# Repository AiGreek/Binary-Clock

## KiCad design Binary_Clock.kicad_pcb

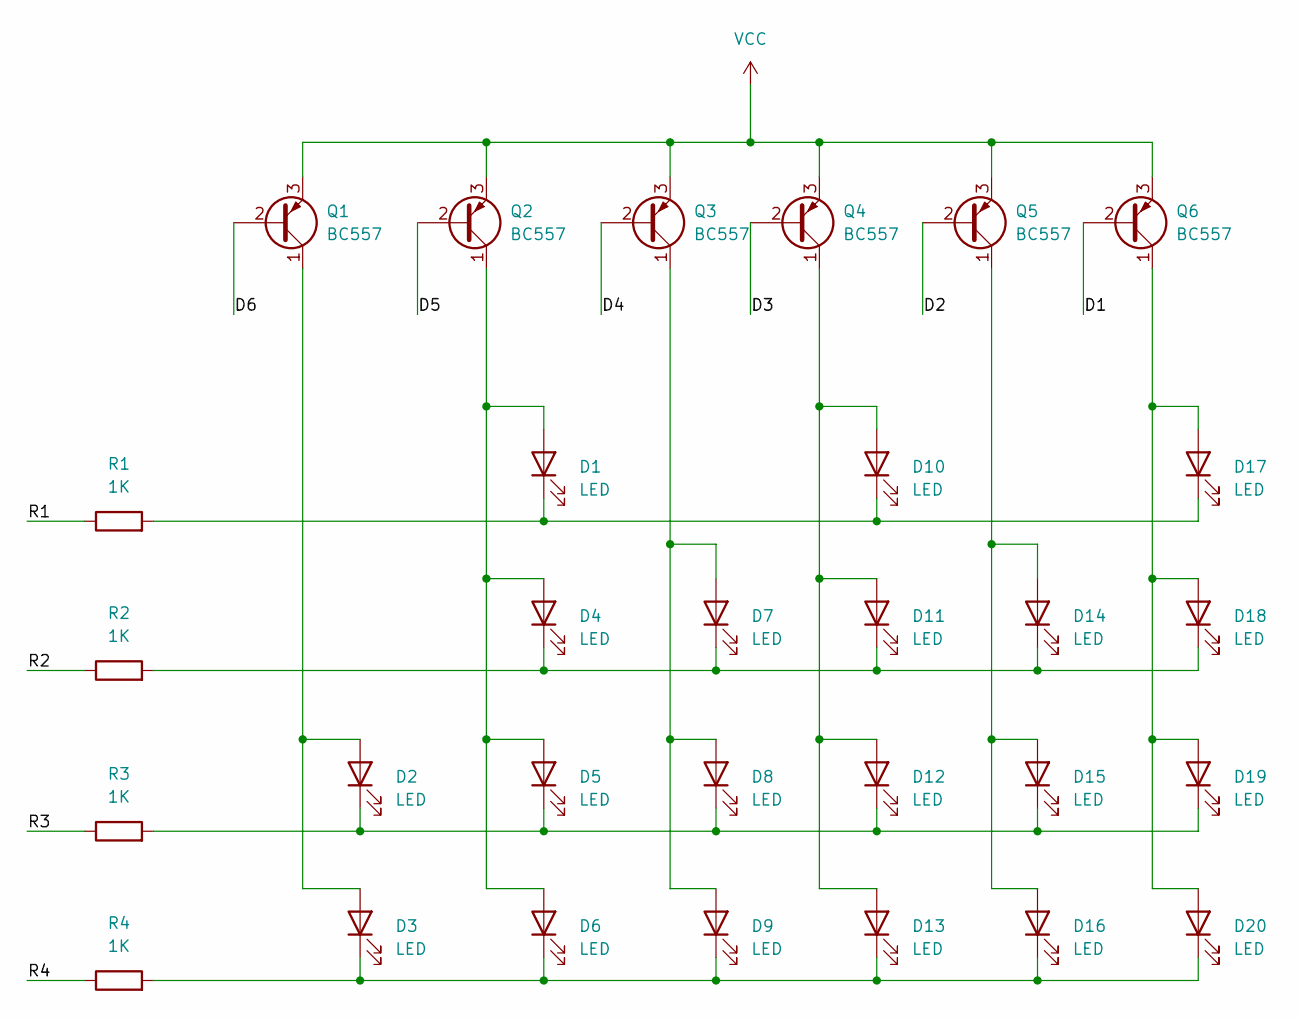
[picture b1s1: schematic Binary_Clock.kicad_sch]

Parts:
D1, D2, D3, D4, D5, D6, D7, D8, D9, D10, D11, D12, D13, D14, D15, D16, D17, D18, D19, D20: LED; LED_D5.0mm
Q1, Q2, Q3, Q4, Q5, Q6: BC557; TO-92_Inline
R1, R2, R3, R4: 1K; R_0805_2012Metric

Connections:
/D1: Q6.2 (B)
/D2: Q5.2 (B)
/D3: Q4.2 (B)
/D4: Q3.2 (B)
/D5: Q2.2 (B)
/D6: Q1.2 (B)
/R1: R1.1
/R2: R2.1
/R3: R3.1
/R4: R4.1
unnamed: D1.1 (K), D10.1 (K), D17.1 (K), R1.2
unnamed: D1.2 (A), D4.2 (A), D5.2 (A), D6.2 (A), Q2.1 (C)
unnamed: D2.2 (A), D3.2 (A), Q1.1 (C)
unnamed: D7.2 (A), D8.2 (A), D9.2 (A), Q3.1 (C)
unnamed: D10.2 (A), D11.2 (A), D12.2 (A), D13.2 (A), Q4.1 (C)
unnamed: D4.1 (K), D7.1 (K), D11.1 (K), D14.1 (K), D18.1 (K), R2.2
unnamed: D2.1 (K), D5.1 (K), D8.1 (K), D12.1 (K), D15.1 (K), D19.1 (K), R3.2
unnamed: D3.1 (K), D6.1 (K), D9.1 (K), D13.1 (K), D16.1 (K), D20.1 (K), R4.2
unnamed: D14.2 (A), D15.2 (A), D16.2 (A), Q5.1 (C)
unnamed: D17.2 (A), D18.2 (A), D19.2 (A), D20.2 (A), Q6.1 (C)
VCC: Q1.3 (E), Q2.3 (E), Q3.3 (E), Q4.3 (E), Q5.3 (E), Q6.3 (E)

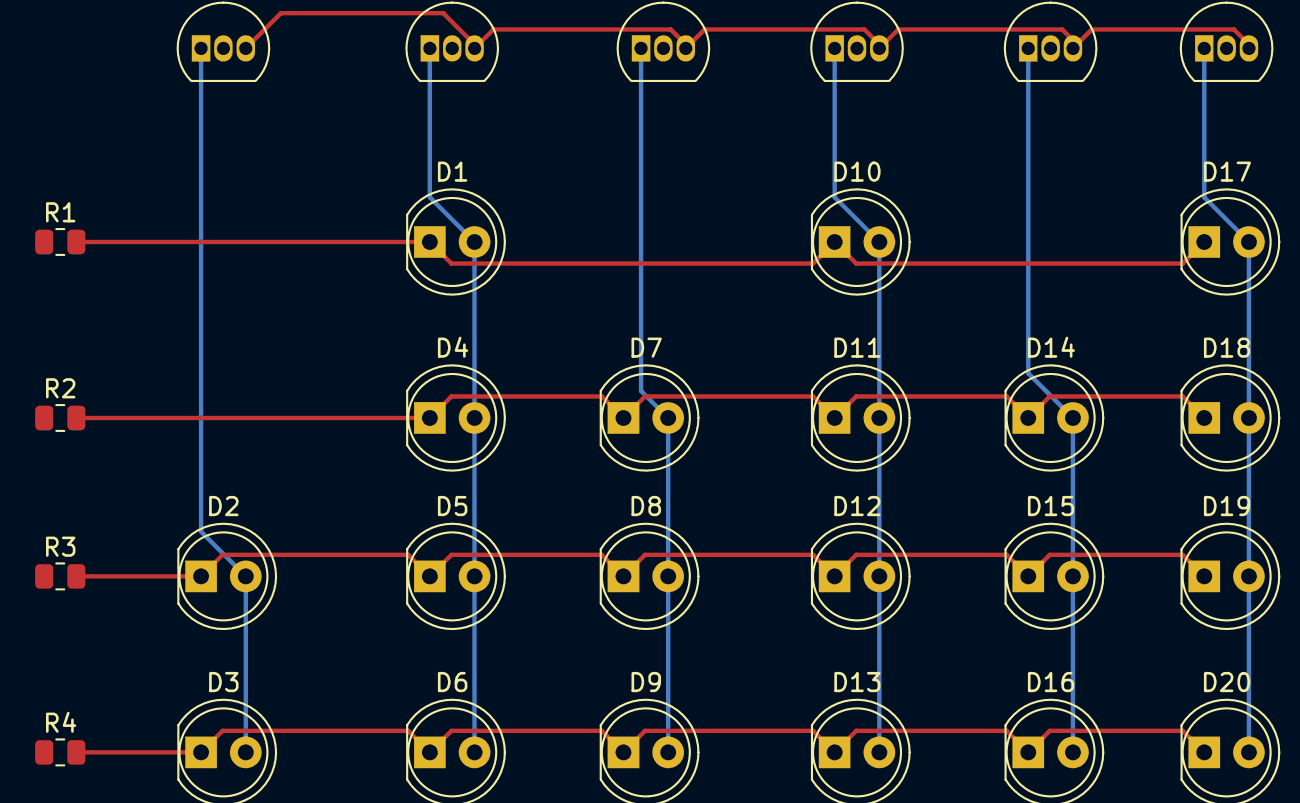
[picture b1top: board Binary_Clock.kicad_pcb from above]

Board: 2 copper layers, 30 parts (0 on the bottom side), 11 nets.
